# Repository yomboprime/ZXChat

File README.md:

# ZXChat
A live chat for ZX Spectrum computers

Revisiones del firmware

r6 Parche para modulos WiFi que no responden OK entre tramas IPD

r5 Parche para evitar que el spectrum pierda el primer byte esporadicamente

r4 Soporta firmware mas reciente del modulo WiFi

r3 Permite usar versiones recientes de Tomcat 8

r2 Permite programar y debuguear en el mismo puerto serie (opcion de intercambiar los puertos serie)

r1 Inicial

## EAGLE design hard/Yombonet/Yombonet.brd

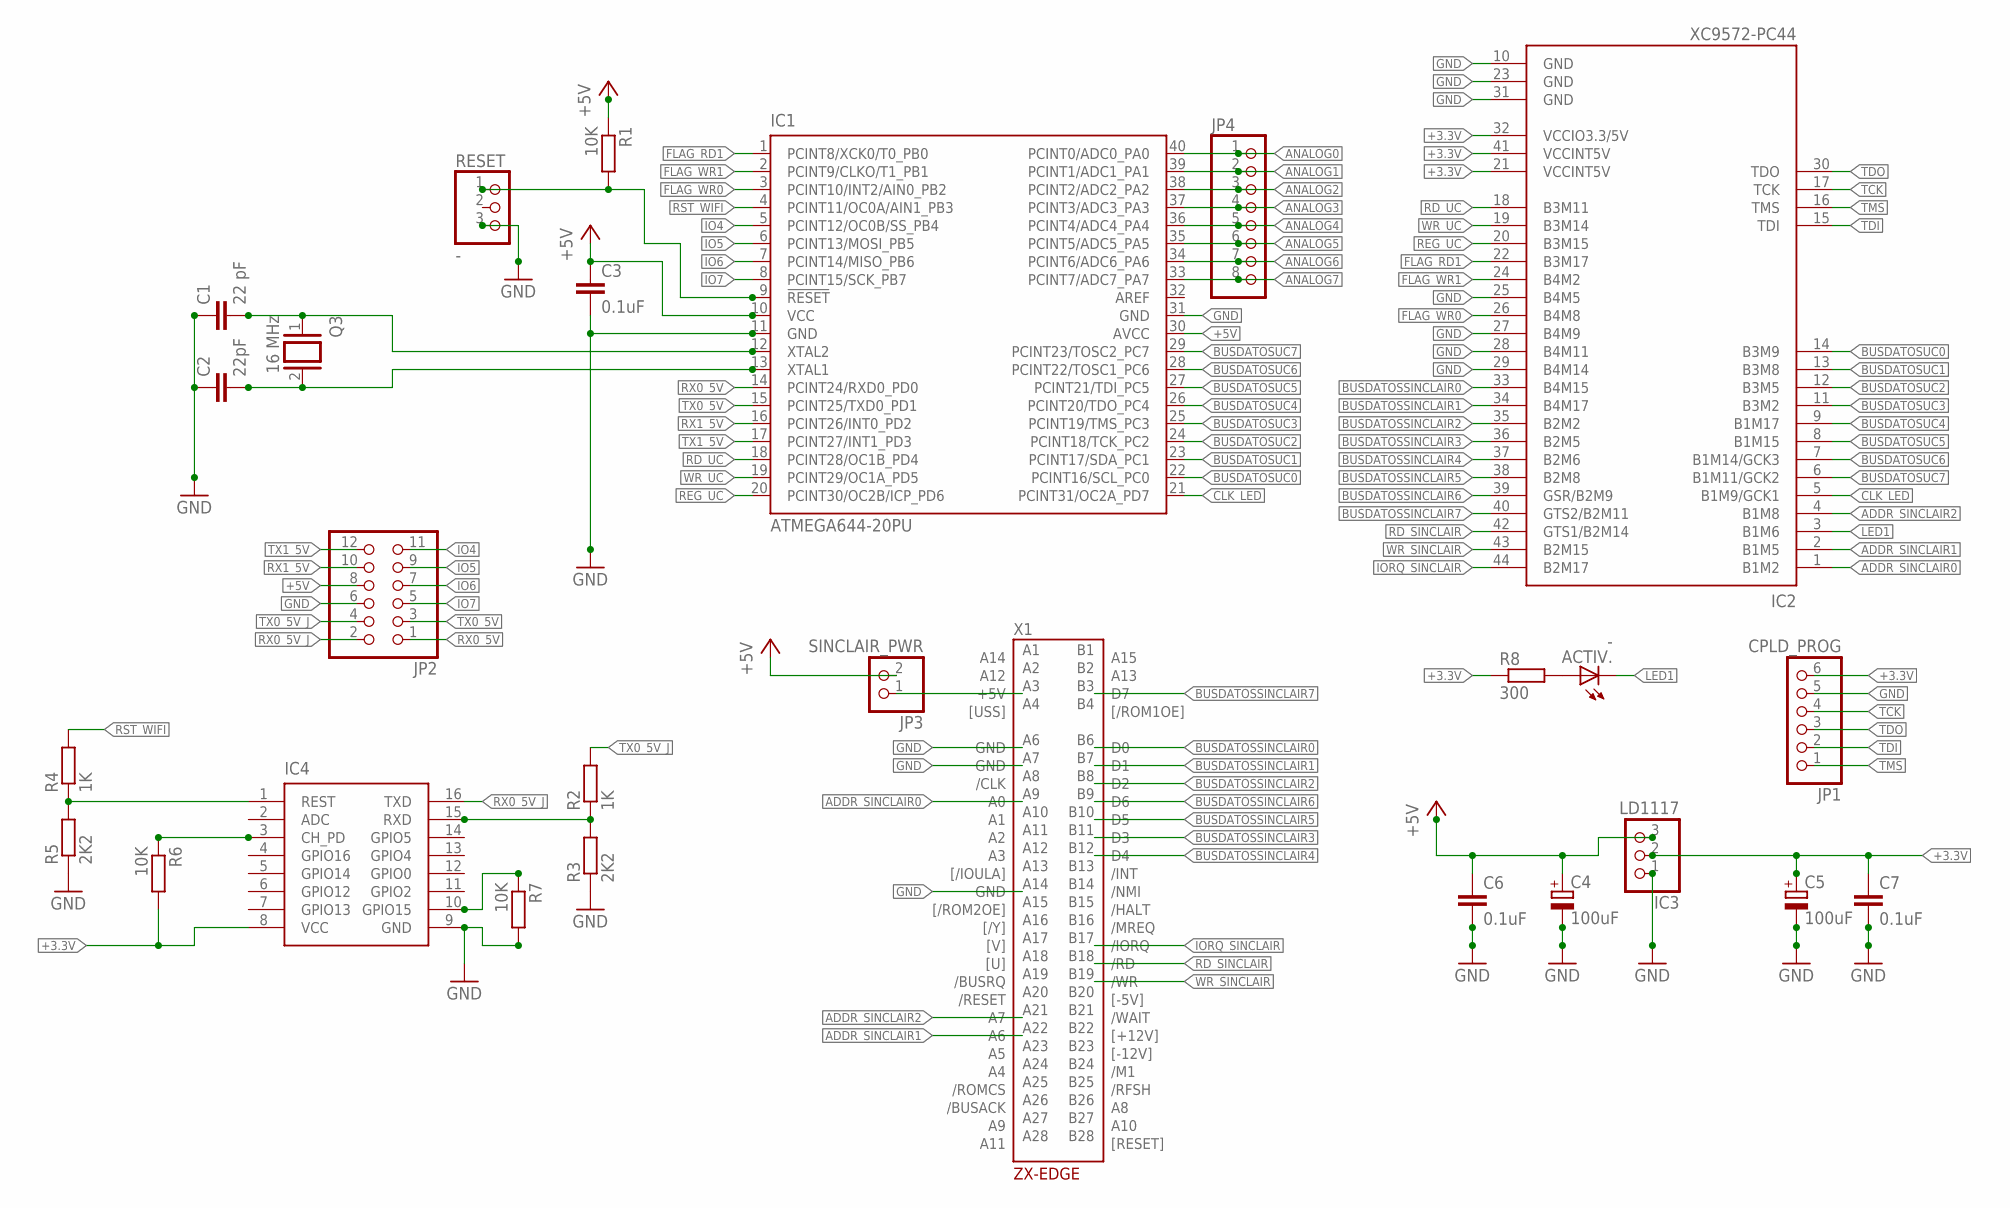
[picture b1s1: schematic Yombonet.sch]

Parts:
ACTIV.: -; LED3MM
C1: 22 pF; C025-024X044
C2: 22pF; C025-024X044
C3, C6, C7: 0.1uF; C025-025X050
C4, C5: 100uF; E2,5-7
IC1: ATMEGA644-20PU; DIL40
IC2: XC9572-PC44; PLCC-S44
IC3: LD1117; 1X03
IC4: ESP-07ESP-07; ESP-07
JP1: CPLD_PROG; 1X06
JP2: PINHD-2X6; 2X06
JP3: SINCLAIR_PWR; 1X02
JP4: PINHD-1X8; 1X08
Q3: 16 MHz; QS
R1, R6, R7: 10K; 0207/10
R2, R4: 1K; 0207/10
R3, R5: 2K2; 0207/10
R8: 300; 0207/10
RESET: -; 1X03
X1: ZX-EDGE; ZX-IFACE

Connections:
+3.3V: C5.+, C7.1, IC2.21 (VCCINT5V), IC2.32 (VCCIO3.3/5V), IC2.41 (VCCINT5V), IC3.2, IC4.8 (VCC), JP1.6, R6.2, R8.1
+5V: C3.1, C4.+, C6.1, IC1.10 (VCC), IC1.30 (AVCC), IC3.3, JP2.8, JP3.2, R1.1
ADDR_SINCLAIR0: IC2.1 (B1M2), X1.A9 (A0)
ADDR_SINCLAIR1: IC2.2 (B1M5), X1.A22 (A6)
ADDR_SINCLAIR2: IC2.4 (B1M8), X1.A21 (A7)
ANALOG0: IC1.40 (PCINT0/ADC0_PA0), JP4.1
ANALOG1: IC1.39 (PCINT1/ADC1_PA1), JP4.2
ANALOG2: IC1.38 (PCINT2/ADC2_PA2), JP4.3
ANALOG3: IC1.37 (PCINT3/ADC3_PA3), JP4.4
ANALOG4: IC1.36 (PCINT4/ADC4_PA4), JP4.5
ANALOG5: IC1.35 (PCINT5/ADC5_PA5), JP4.6
ANALOG6: IC1.34 (PCINT6/ADC6_PA6), JP4.7
ANALOG7: IC1.33 (PCINT7/ADC7_PA7), JP4.8
BUSDATOSSINCLAIR0: IC2.33 (B4M15), X1.B6 (D0)
BUSDATOSSINCLAIR1: IC2.34 (B4M17), X1.B7 (D1)
BUSDATOSSINCLAIR2: IC2.35 (B2M2), X1.B8 (D2)
BUSDATOSSINCLAIR3: IC2.36 (B2M5), X1.B11 (D3)
BUSDATOSSINCLAIR4: IC2.37 (B2M6), X1.B12 (D4)
BUSDATOSSINCLAIR5: IC2.38 (B2M8), X1.B10 (D5)
BUSDATOSSINCLAIR6: IC2.39 (GSR/B2M9), X1.B9 (D6)
BUSDATOSSINCLAIR7: IC2.40 (GTS2/B2M11), X1.B3 (D7)
BUSDATOSUC0: IC1.22 (PCINT16/SCL_PC0), IC2.14 (B3M9)
BUSDATOSUC1: IC1.23 (PCINT17/SDA_PC1), IC2.13 (B3M8)
BUSDATOSUC2: IC1.24 (PCINT18/TCK_PC2), IC2.12 (B3M5)
BUSDATOSUC3: IC1.25 (PCINT19/TMS_PC3), IC2.11 (B3M2)
BUSDATOSUC4: IC1.26 (PCINT20/TDO_PC4), IC2.9 (B1M17)
BUSDATOSUC5: IC1.27 (PCINT21/TDI_PC5), IC2.8 (B1M15)
BUSDATOSUC6: IC1.28 (PCINT22/TOSC1_PC6), IC2.7 (B1M14/GCK3)
BUSDATOSUC7: IC1.29 (PCINT23/TOSC2_PC7), IC2.6 (B1M11/GCK2)
CH_PH_PULLUP: IC4.3 (CH_PD), R6.1
CLK_LED: IC1.21 (PCINT31/OC2A_PD7), IC2.5 (B1M9/GCK1)
FLAG_RD1: IC1.1 (PCINT8/XCK0/T0_PB0), IC2.22 (B3M17)
FLAG_WR0: IC1.3 (PCINT10/INT2/AIN0_PB2), IC2.26 (B4M8)
FLAG_WR1: IC1.2 (PCINT9/CLKO/T1_PB1), IC2.24 (B4M2)
GND: C1.1, C2.1, C3.2, C4.-, C5.-, C6.2, C7.2, IC1.11 (GND), IC1.31 (GND), IC2.10 (GND), IC2.23 (GND), IC2.25 (B4M5), IC2.27 (B4M9), IC2.28 (B4M11), IC2.29 (B4M14), IC2.31 (GND), IC3.1, IC4.9 (GND), JP1.5, JP2.6, R3.1, R5.1, R7.2, RESET.3, X1.A6 (GND), X1.A7 (GND), X1.A14 (GND)
GPIO15_PULLDOWN: IC4.10 (GPIO15), R7.1
IO4: IC1.5 (PCINT12/OC0B/SS_PB4), JP2.11
IO5: IC1.6 (PCINT13/MOSI_PB5), JP2.9
IO6: IC1.7 (PCINT14/MISO_PB6), JP2.7
IO7: IC1.8 (PCINT15/SCK_PB7), JP2.5
IORQ_SINCLAIR: IC2.44 (B2M17), X1.B17 (/IORQ)
LED1: ACTIV..K (C), IC2.3 (B1M6)
unnamed: IC4.15 (RXD), R2.1, R3.2
unnamed: ACTIV..A, R8.2
unnamed: JP3.1, X1.A3 (+5V)
OSC1: C1.2, IC1.12 (XTAL2), Q3.1
OSC2: C2.2, IC1.13 (XTAL1), Q3.2
RD_SINCLAIR: IC2.42 (GTS1/B2M14), X1.B18 (/RD)
RD_UC: IC1.18 (PCINT28/OC1B_PD4), IC2.18 (B3M11)
REG_UC: IC1.20 (PCINT30/OC2B/ICP_PD6), IC2.20 (B3M15)
RESET_UC: IC1.9 (!RESET), R1.2, RESET.1
RST_WIFI: IC1.4 (PCINT11/OC0A/AIN1_PB3), R4.2
RST_WIFI_3.3V: IC4.1 (REST), R4.1, R5.2
RX0_5V: IC1.14 (PCINT24/RXD0_PD0), JP2.1
RX0_5V_J: IC4.16 (TXD), JP2.2
RX1_5V: IC1.16 (PCINT26/INT0_PD2), JP2.10
TCK: IC2.17 (TCK), JP1.4
TDI: IC2.15 (TDI), JP1.2
TDO: IC2.30 (TDO), JP1.3
TMS: IC2.16 (TMS), JP1.1
TX0_5V: IC1.15 (PCINT25/TXD0_PD1), JP2.3
TX0_5V_J: JP2.4, R2.2
TX1_5V: IC1.17 (PCINT27/INT1_PD3), JP2.12
WR_SINCLAIR: IC2.43 (B2M15), X1.B19 (/WR)
WR_UC: IC1.19 (PCINT29/OC1A_PD5), IC2.19 (B3M14)

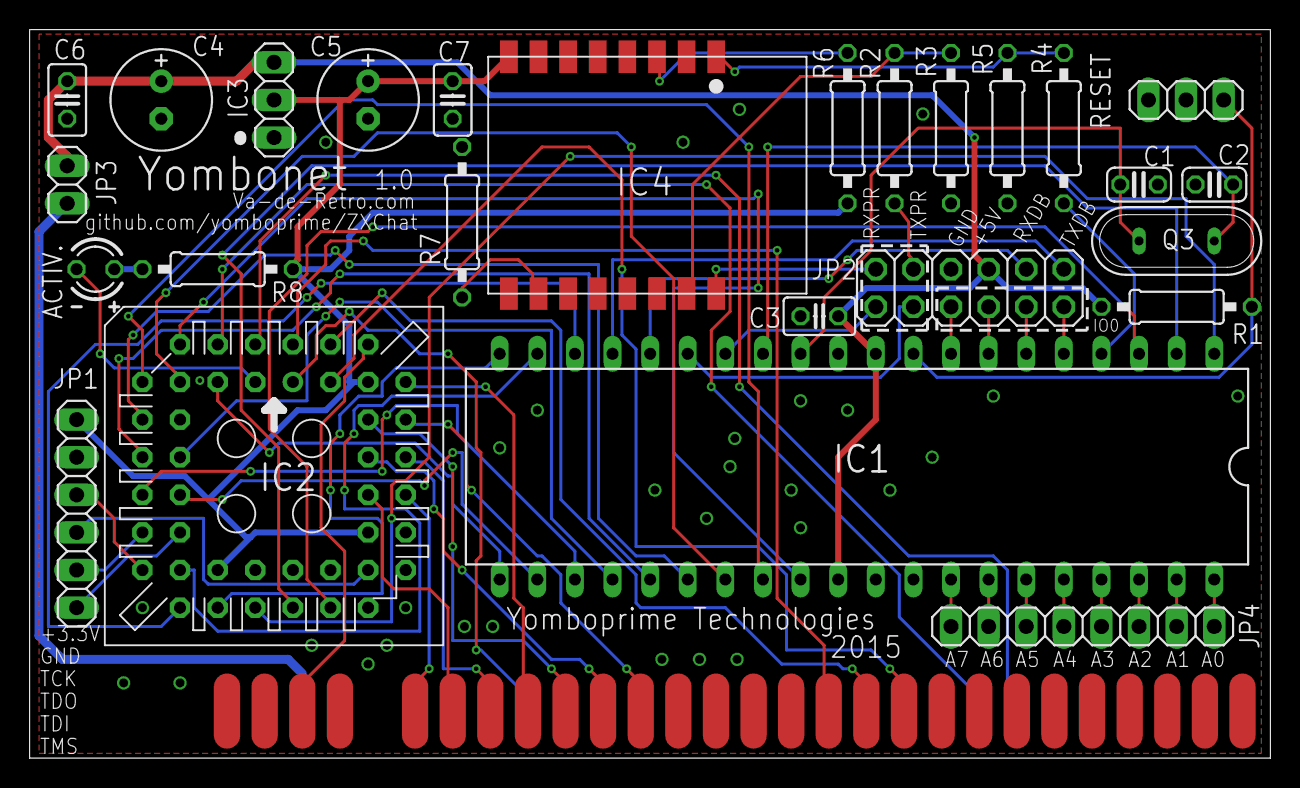
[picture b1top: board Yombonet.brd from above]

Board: 4 copper layers, 83.8 x 49.2 mm, 27 parts (0 on the bottom side), 65 nets.

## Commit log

2015-03-19 Commit inicial
2015-03-19 Esquema: añadido conector de programacion de cpld. Prueba de posicionado.
2015-03-20 Añadido conector Edge y conector del LD1117 vertical
2015-03-20 Faltaba el fichero de la PCB de eagle
2015-03-21 Esquema: Añadido módulo wifi y conectores I/O
2015-03-21 Arregladas algunas señales que no estaban conectadas en el cpld, módulo wifi y conector edge.
2015-03-21 Modificada resistencia R8, el valor correcto es 300 Ohm
2015-03-24 Subiendo presupuesto
2015-03-24 Actualizado envio de materiales farnell
2015-03-25 CPLD software: Cambiado el CPLD a la version de 3.3V (XC9572XL)
2015-03-25 Version preliminar de la PCB (PR3)
2015-03-25 Actualizado presupuesto, cambios menores (no hay cambios en precios)
2015-03-25 Subiendo gerbers preliminares (PR3)
2015-03-28 Codigo CPLD: Cambiado A0A7A6 por A7A6A0, el patillaje de estas lineas ya no es igual que en el prototipo.
2015-03-28 PCB: Anyadidas dos vias de masa
2015-03-29 PCB: Cambiado nick de acf76es por retrocant
2015-03-29 Subiendo presupuesto ebay-aliexpress
2015-04-02 Esquematico: Cambiados varios conectores a uno solo de 2x6
2015-04-04 PCB: Cambios en pistas, serigrafia y posicion vias
2015-04-10 Presupuesto: Actualizado link al zocalo PLCC44, que era SMD erroneamente. Ahora es through hole.
2015-04-10 PCB: Anadidas mas vias de plano de masa
2015-04-10 PCB: Actualizado silkscreen con nick de vidamia
2015-04-10 Presupuesto: Actualizado link del Atmega32A
2015-04-10 Subiendo fichero de materiales, Bill Of Materials (BOM)
2015-04-11 BOM: Componentes agrupados por valor.
2015-04-13 Actualizadas compras
2015-04-14 Doc: Esquema CPLD
2015-04-15 Doc: Actualizado estado compra. Borrado fichero materiales farnell
2015-04-16 PCB: modificada una pista y anyadidas 3 vias. Version subida a Seeedstudio.
2015-04-16 PCB: Movidos nicks a silkscreen de abajo. Ahora si, enviada a Seeed, r1
2015-04-18 ZXChat: Cambios menores, prueba de envio de codigo de error al spectrum
2015-04-21 Subido soporte arduino para mighty-1284p y Atmega32A
2015-04-21 Actualizada lista de compras
2015-04-21 Empezadas instrucciones con el formato final
2015-04-29 Instrucciones implementadas: Obtener numero de revision, activar/desactivar debug, y conectar a wifi.
2015-04-29 ZXBasic: Funciones recibirCadena() y transmitirCadena()
2015-04-29 Reorganizando codigo del cliente zchat en ficheros
2015-05-08 Mejorado esquema CPLD
2015-05-08 Actualizado fichero compras con ultimos componentes llegados
2015-05-08 Empezado el menu de ZXChat
2015-05-10 Mejoras docs
2015-05-10 Implementadas todas las opciones de menu. Ya accede a YomboServer. Programa ZXChat practicamente terminado.
2015-05-12 Añadiendo esquema, retoques documentacion firmware
2015-05-19 Subiendo YomboServer actualizado con ultimos cambios (control de tamaño de mensajes enviados)
2015-06-02 ZXuiter (tramas HTTP POST anyadidas). Ejemplos nuevos.
2015-07-18 Yombonet 1.0 funcionando con el microcontrolador Atmega1284P en vez del Atmega32A
2015-07-30 Corregido bug de limitar el tamanyo de la salida.
2015-10-19 Firmware r2
2015-10-19 Arreglado fallo de sintaxis en r2
2015-10-19 Firmware r3: Admite servidor Tomcat 8
2015-10-19 Actualizado README con versiones del firmware.
2015-10-20 Arreglada velocidad baudios, estaba fija
2015-10-20 Yomboserver: anyadida fecha a mensajes
2015-10-20 Cliente chat spectrum r2: Texto pequenyo, mas opciones
2015-10-20 Firmware r4
2015-10-20 Corrigiendo define olvidado. Firmware r4
2015-10-21 Bug valores boleanos. Salida de los primeros 10 bytes para error esporadico.
2015-10-22 Comentando #define PUERTOS_SERIE_PROTOTIPO
2015-10-23 Quitando debug de timestamp, poniendolo en sketch YombonetPruebaFermars
2015-10-24 Restaurando sketch Yombonet para ver si se arregla error de conexion.
2015-10-25 Comentando PUERTOS_SERIE_PROTOTIPO
2015-10-25 Echando atras Prueba Fermars
2015-10-25 Parcheando programa y server para que el spectrum anyada un espacio al timestamp.
2015-10-26 Parche para evitar perdida de primer caracter, arreglado.
2015-10-31 Actualizando BOM
2015-10-31 Parche para modulos WiFi que no responden OK entre tramas IPD
2015-11-01 r6, r3. Solucionado bug de pulsar reset al inicio. Ahora no se imprimen codigos de error.
2015-11-02 Quitando d nuevo puertos serie prorotipo
2015-11-02 Accion historial en el server.
2015-11-04 Volviendo a comentar lectura registro control para evitar boton reset
2015-11-05 Faltaban los zócalos en el Bill Of Materials
2015-12-11 ZXuiter r2, permite hasta tres tareas o bots en botize
